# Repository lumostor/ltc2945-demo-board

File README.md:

# ltc2924-demo-board
ltc2924 Wide Range I 2C Power Monitor demo board

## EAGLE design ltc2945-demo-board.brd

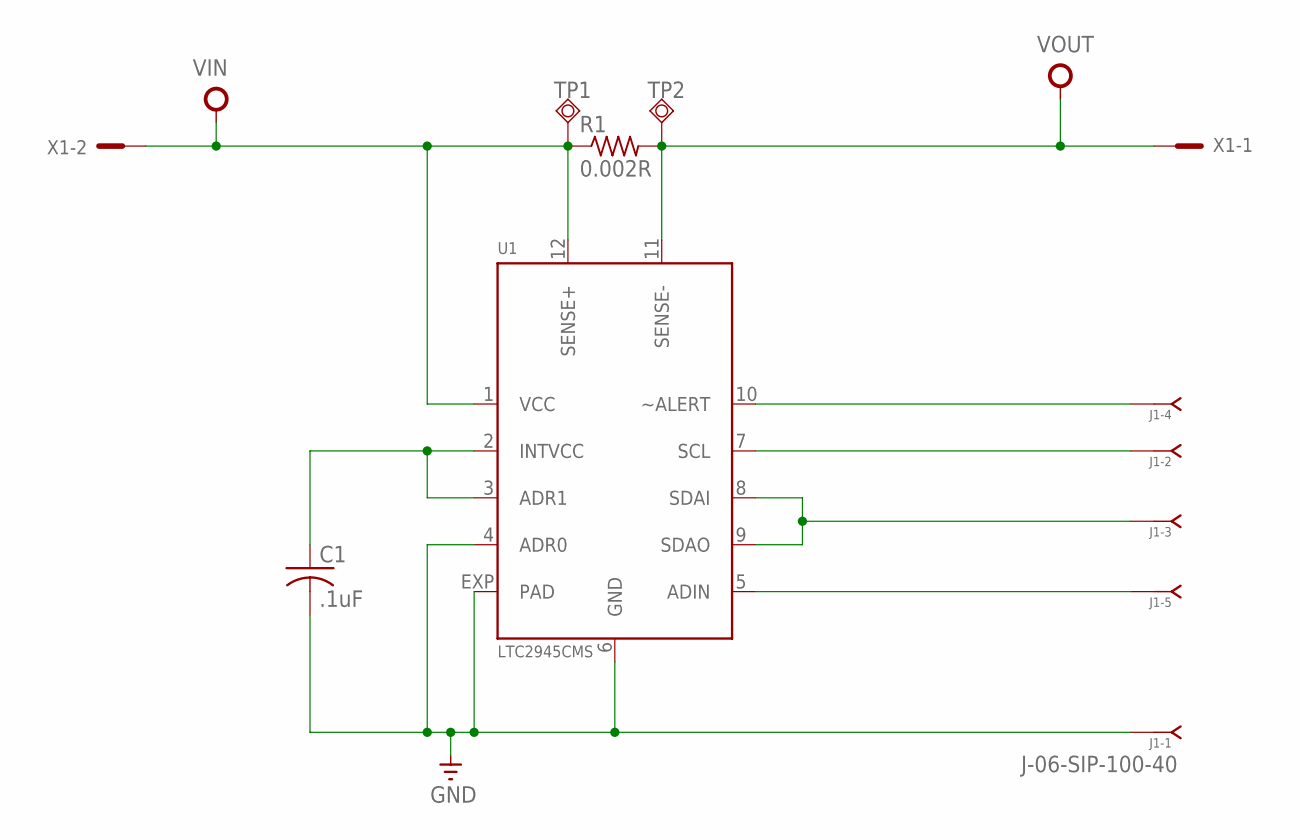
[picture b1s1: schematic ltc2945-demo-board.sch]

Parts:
C1: .1uF; C0603
J1: J-06-SIP-100-40; SIP-100-06-40
R1: 0.002R; R2512
TP1, TP2: TPSQPAD1-17; P1-17
U1: LTC2945CMS; MSOP12
X1: MCV_05/2-G-2,5; MC2

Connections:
GND: C1.2, J1.1, U1.4 (ADR0), U1.6 (GND), U1.EXP (PAD)
unnamed: J1.5, U1.5 (ADIN)
unnamed: J1.3, U1.8 (SDAI), U1.9 (SDAO)
unnamed: C1.1, U1.2 (INTVCC), U1.3 (ADR1)
unnamed: J1.4, U1.10 (~ALERT)
unnamed: J1.2, U1.7 (SCL)
VIN: R1.1, TP1.TP, U1.1 (VCC), U1.12 (SENSE+), X1.2
VOUT: R1.2, TP2.TP, U1.11 (SENSE-), X1.1

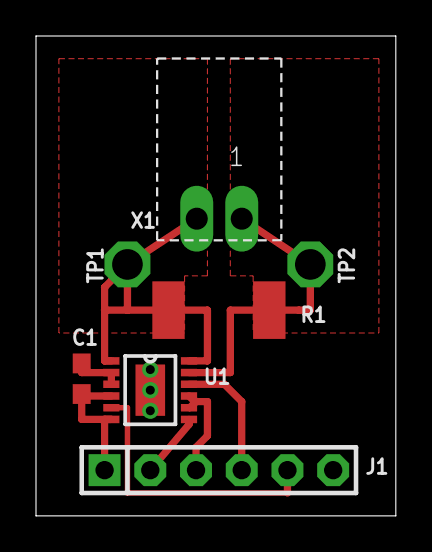
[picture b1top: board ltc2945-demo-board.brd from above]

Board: 2 copper layers, 20.0 x 26.7 mm, 7 parts (0 on the bottom side), 8 nets.

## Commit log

2016-03-28 v1.0 sent to oshpark
2016-03-28 added OSHpark board images

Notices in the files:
ltc2945-demo-board.brd:
(c) 2016 Luc Chouinard
parts and their libraries:
con-headers-jp: Copyright (C) 2008, Bob Starr
